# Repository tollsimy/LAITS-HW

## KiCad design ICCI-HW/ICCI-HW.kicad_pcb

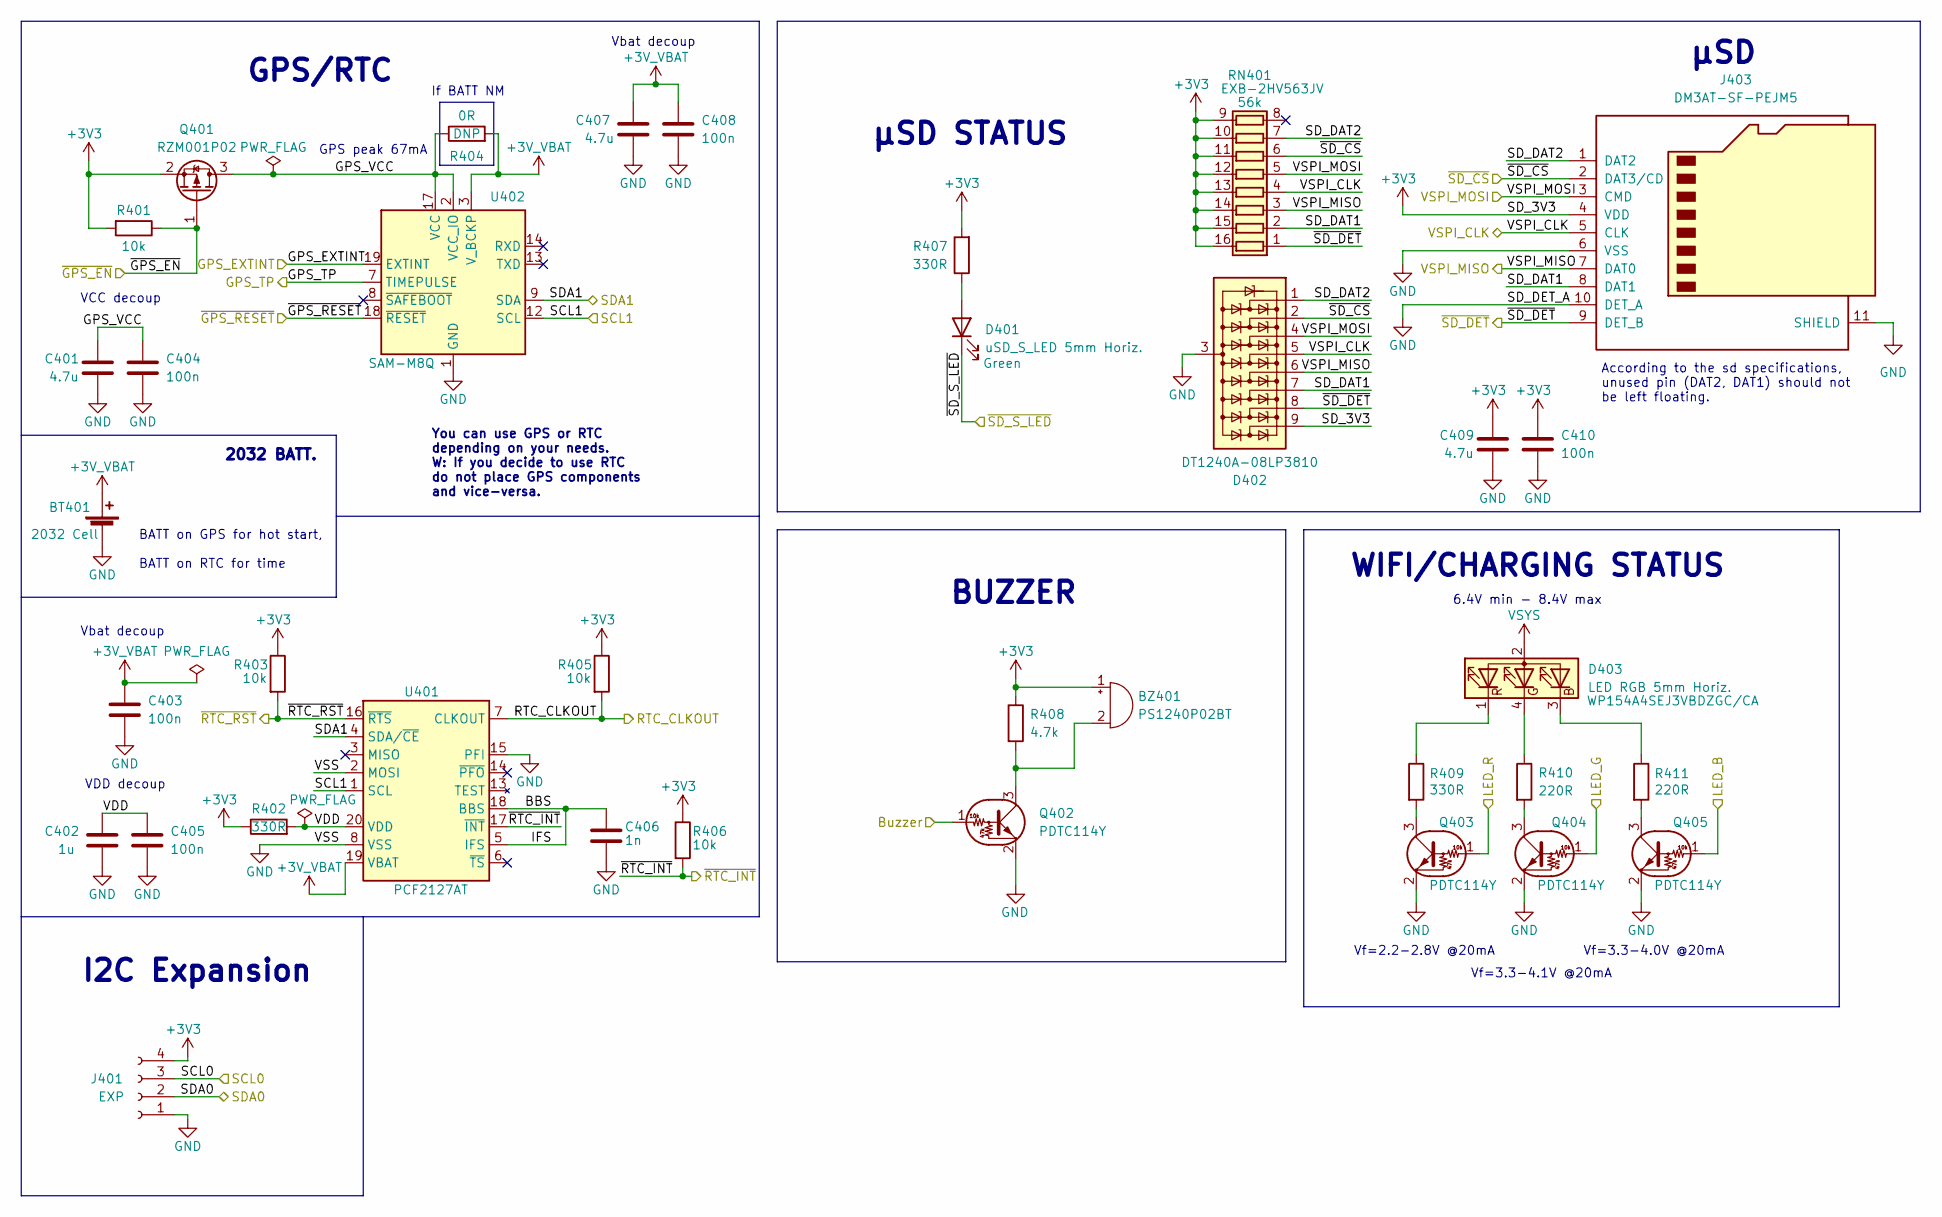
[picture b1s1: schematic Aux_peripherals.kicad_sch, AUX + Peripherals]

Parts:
BT401: 2032 Cell; BatteryHolder_Keystone_3034_1x20mm
BZ401: PS1240P02BT; Buzzer_TDK_PS1240P02BT_D12.2mm_H6.5mm
C401, C407, C409: 4.7u; C_0603_1608Metric
C402: 1u; C_0603_1608Metric
C403, C404, C405, C408, C410: 100n; C_0603_1608Metric
C406: 1n; C_0603_1608Metric
D401: uSD_S_LED 5mm Horiz.; LED_D5.0mm_Horizontal_O3.81mm_Z3.0mm
D402: DT1240A-08LP3810; ICCI_UDFN-9_1.0x3.8mm_P0.5mm
D403: LED RGB 5mm Horiz.; LED_D5.0mm-4_RGB_Staggered_Pins_Horizontal
J401: EXP; PinSocket_2x02_P2.54mm_Horizontal
J403: DM3AT-SF-PEJM5; ICCI_microSD_HC_Hirose_DM3AT-SF-PEJM5
Q401: RZM001P02
Q402, Q403, Q404, Q405: PDTC114Y; SOT-23
R401, R403, R405, R406: 10k; R_0603_1608Metric
R402, R407, R409: 330R; R_0603_1608Metric
R404: 0R; R_0603_1608Metric
R408: 4.7k; R_0603_1608Metric
R410, R411: 220R; R_0603_1608Metric
RN401: 56k; R_Array_Convex_8x0602
U401: PCF2127AT
U402: SAM-M8Q; ICCI_ublox_SAM-M8Q

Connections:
+3V0: BT401.1 (+), C403.1, C407.1, C408.1, R404.2, U401.19 (VBAT), U402.3 (V_BCKP); also elsewhere on the board
+3V3: BZ401.1 (-), C409.1, C410.1, D402.9 (K8), J401.4, J403.4 (VDD), Q401.2 (S), R401.2, R402.1, R403.1, R405.1, R406.1, R407.2, R408.1, RN401.9 (R8.2), RN401.10 (R7.2), RN401.11 (R6.2), RN401.12 (R5.2), RN401.13 (R4.2), RN401.14 (R3.2), RN401.15 (R2.2), RN401.16 (R1.2); also elsewhere on the board
/AUX + Peripherals/BBS: C406.1, U401.5 (IFS), U401.18 (BBS)
/AUX + Peripherals/GPS_EXTINT: U402.19 (EXTINT); also elsewhere on the board
/AUX + Peripherals/GPS_TP: U402.7 (TIMEPULSE); also elsewhere on the board
/AUX + Peripherals/GPS_VCC: C401.1, C404.1, Q401.3 (D), R404.1, U402.2 (VCC_IO), U402.17 (VCC)
/AUX + Peripherals/LED_B: Q405.1 (B); also elsewhere on the board
/AUX + Peripherals/LED_G: Q404.1 (B); also elsewhere on the board
/AUX + Peripherals/LED_R: Q403.1 (B); also elsewhere on the board
/AUX + Peripherals/RTC_CLKOUT: R405.2, U401.7 (CLKOUT); also elsewhere on the board
/AUX + Peripherals/SCL0: J401.3; also elsewhere on the board
/AUX + Peripherals/SCL1: U401.1 (SCL), U402.12 (SCL); also elsewhere on the board
/AUX + Peripherals/SDA0: J401.2; also elsewhere on the board
/AUX + Peripherals/SDA1: U401.4 (SDA/~CE), U402.9 (SDA); also elsewhere on the board
/AUX + Peripherals/SD_DAT1: D402.7 (K6), J403.8 (DAT1), RN401.2 (R2.1)
/AUX + Peripherals/SD_DAT2: D402.1 (K1), J403.1 (DAT2), RN401.7 (R7.1)
/AUX + Peripherals/VDD: C402.1, C405.1, R402.2, U401.20 (VDD)
/AUX + Peripherals/VSPI_CLK: D402.5 (K4), J403.5 (CLK), RN401.4 (R4.1); also elsewhere on the board
/AUX + Peripherals/VSPI_MISO: D402.6 (K5), J403.7 (DAT0), RN401.3 (R3.1); also elsewhere on the board
/AUX + Peripherals/VSPI_MOSI: D402.4 (K3), J403.3 (CMD), RN401.5 (R5.1); also elsewhere on the board
/AUX + Peripherals/~GPS_EN: Q401.1 (G), R401.1; also elsewhere on the board
/AUX + Peripherals/~GPS_RESET: U402.18 (~RESET); also elsewhere on the board
/AUX + Peripherals/~RTC_INT: R406.2, U401.17 (~INT); also elsewhere on the board
/AUX + Peripherals/~RTC_RST: R403.2, U401.16 (~RTS); also elsewhere on the board
/AUX + Peripherals/~SD_CS: D402.2 (K2), J403.2 (DAT3/CD), RN401.6 (R6.1); also elsewhere on the board
/AUX + Peripherals/~SD_DET: D402.8 (K7), J403.9 (DET_B), RN401.1 (R1.1); also elsewhere on the board
/AUX + Peripherals/~SD_S_LED: D401.1 (K); also elsewhere on the board
/ESP/Buzzer: Q402.1 (B); also elsewhere on the board
GND: BT401.2 (-), C401.2, C402.2, C403.2, C404.2, C405.2, C406.2, C407.2, C408.2, C409.2, C410.2, D402.3 (A), J401.1, J403.6 (VSS), J403.10 (DET_A), J403.11 (SHIELD), Q402.2 (E), Q403.2 (E), Q404.2 (E), Q405.2 (E), U401.2 (MOSI), U401.8 (VSS), U401.15 (PFI), U402.1 (GND), U402.4 (GND), U402.5 (GND), U402.6 (GND), U402.10 (GND), U402.11 (GND), U402.15 (GND), U402.16 (GND), U402.20 (GND); also elsewhere on the board
unnamed: BZ401.2 (+), Q402.3 (C), R408.2
unnamed: D401.2 (A), R407.1
unnamed: D403.1 (RK), R409.1
unnamed: D403.3 (BK), R411.1
unnamed: D403.4 (GK), R410.1
unnamed: Q403.3 (C), R409.2
unnamed: Q404.3 (C), R410.2
unnamed: Q405.3 (C), R411.2
VCC: D403.2 (A); also elsewhere on the board

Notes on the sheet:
VCC decoup
Vbat decoup
GPS/RTC
According to the sd specifications, unused pin (DAT2, DAT1) should not be left floating.
You can use GPS or RTC depending on your needs. W: If you decide to use RTC do not place GPS components and vice-versa.
BUZZER
I2C Expansion
6.4V min - 8.4V max
Vf=2.2-2.8V @20mA
If BATT NM
BATT on GPS for hot start, BATT on RTC for time
GPS peak 67mA
μSD STATUS
VDD decoup
Vf=3.3-4.1V @20mA
2032 BATT.
Vf=3.3-4.0V @20mA
WIFI/CHARGING STATUS
μSD

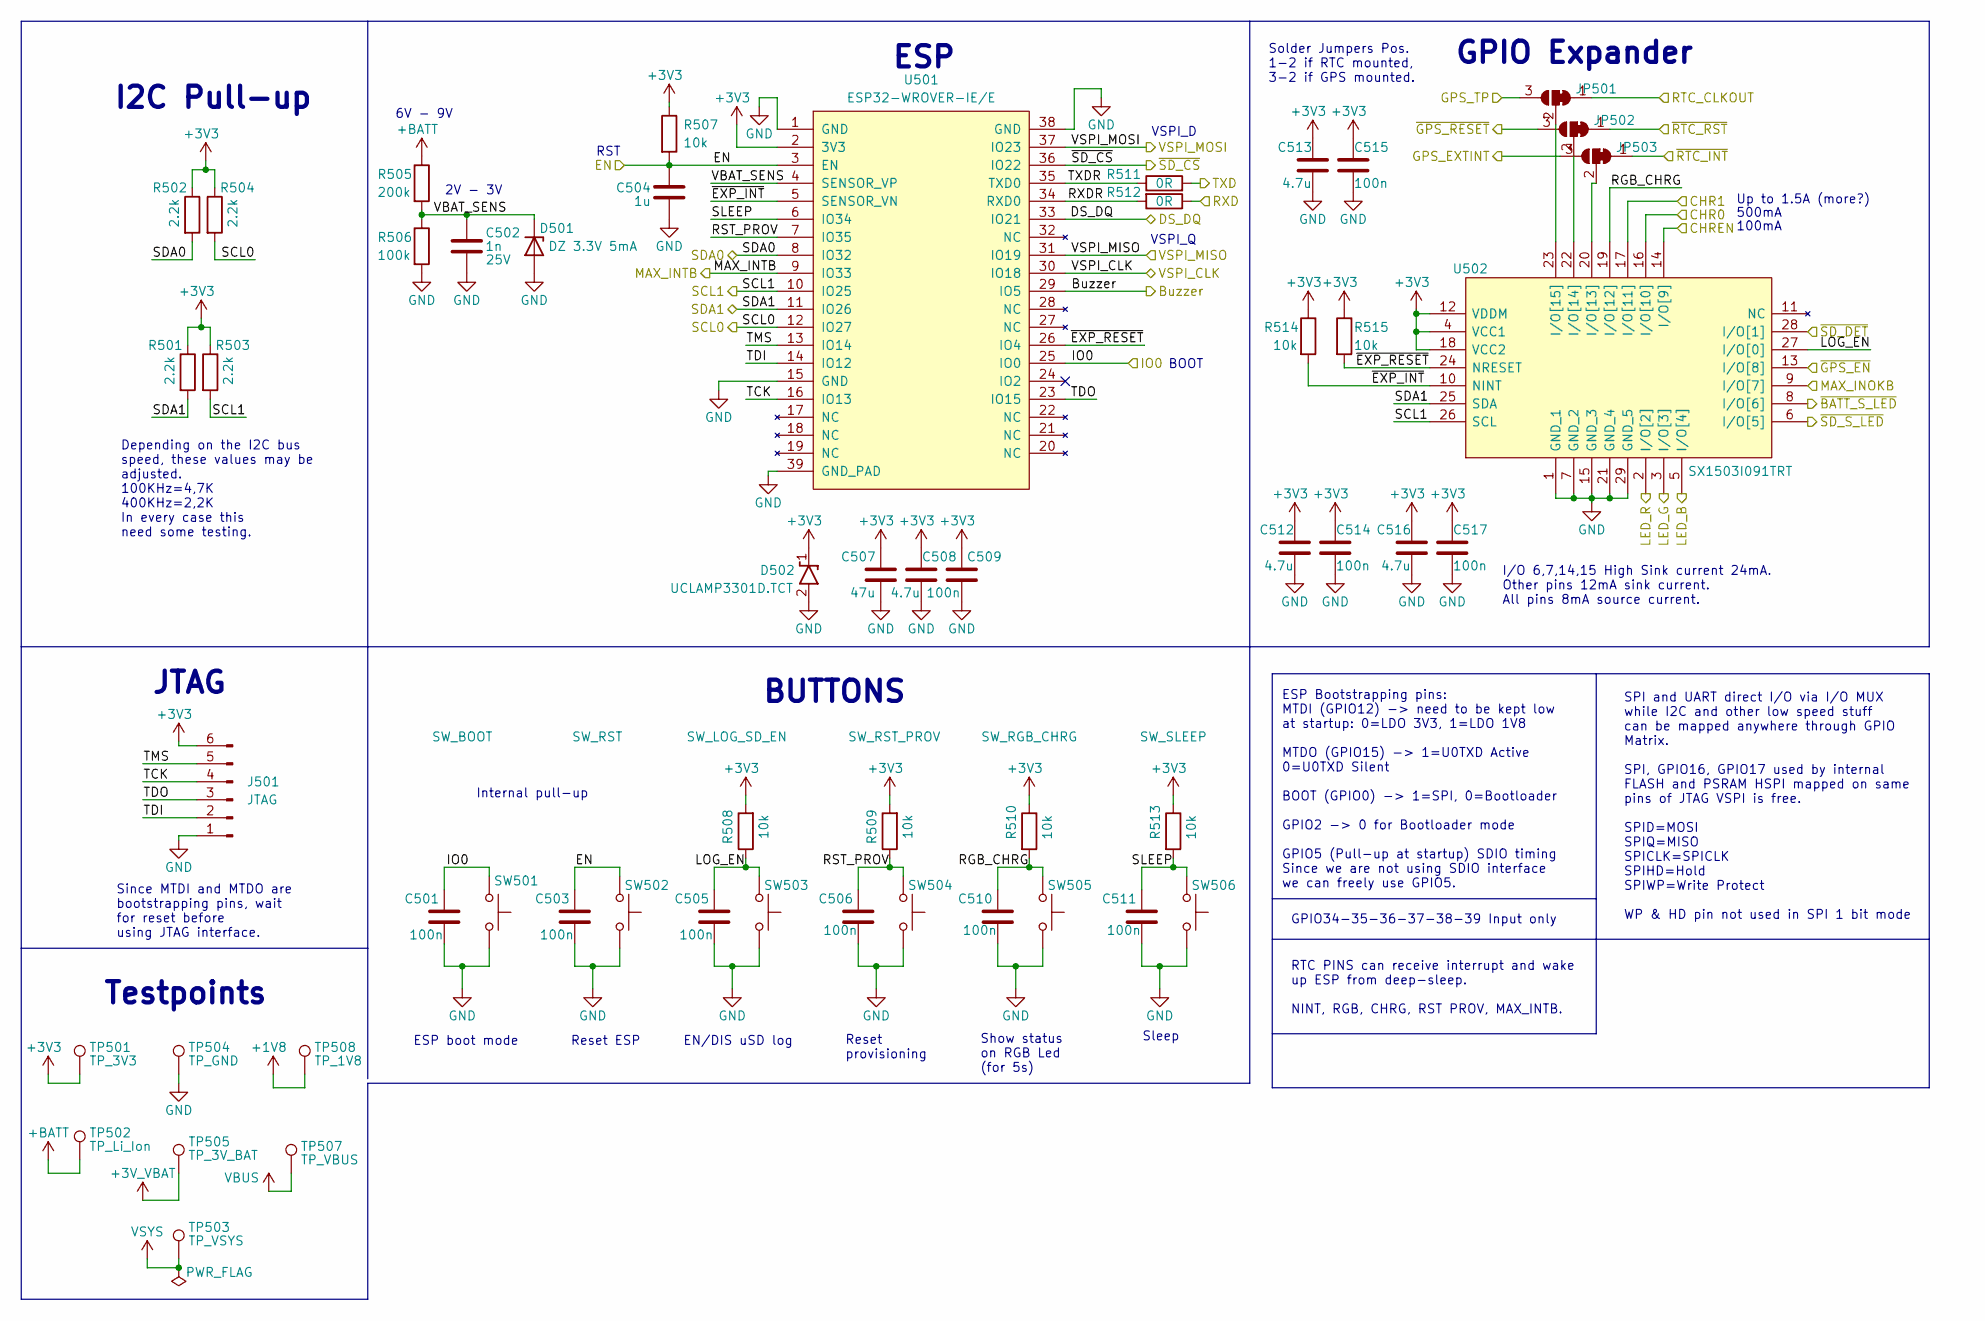
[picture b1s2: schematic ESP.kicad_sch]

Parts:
C501, C503, C505, C506, C509, C510, C511, C514, C515, C517: 100n; C_0603_1608Metric
C502: 1n; C_0603_1608Metric; Voltage Rating 25V
C504: 1u; C_0603_1608Metric
C507: 47u; C_1210_3225Metric
C508, C512, C513, C516: 4.7u; C_0603_1608Metric
D501: DZ 3.3V 5mA; D_SOD-923
D502: UCLAMP3301D.TCT; D_SOD-323
J501: JTAG; JST_B6B-XH-A
JP501, JP502, JP503: SolderJumper_3_Bridged12; SolderJumper-3_P1.3mm_Open_RoundedPad1.0x1.5mm_NumberLabels
R501, R502, R503, R504: 2.2k; R_0603_1608Metric
R505: 200k; R_0603_1608Metric
R506: 100k; R_0603_1608Metric
R507, R508, R509, R510, R513, R514, R515: 10k; R_0603_1608Metric
R511, R512: 0R; R_0603_1608Metric
SW501: SW_BOOT; SW_Tactile_SPST_Angled_PTS645Vx83-2LFS
SW502: SW_RST; SW_Tactile_SPST_Angled_PTS645Vx83-2LFS
SW503: SW_LOG_SD_EN; SW_Tactile_SPST_Angled_PTS645Vx83-2LFS
SW504: SW_RST_PROV; SW_Tactile_SPST_Angled_PTS645Vx83-2LFS
SW505: SW_RGB_CHRG; SW_Tactile_SPST_Angled_PTS645Vx83-2LFS
SW506: SW_SLEEP; SW_Tactile_SPST_Angled_PTS645Vx83-2LFS
TP501: TP_3V3; TestPoint_THTPad_D1.5mm_Drill0.7mm
TP502: TP_Li_Ion; TestPoint_THTPad_D1.5mm_Drill0.7mm
TP503: TP_VSYS; TestPoint_THTPad_D1.5mm_Drill0.7mm
TP504: TP_GND; TestPoint_THTPad_D1.5mm_Drill0.7mm
TP505: TP_3V_BAT; TestPoint_THTPad_D1.5mm_Drill0.7mm
TP507: TP_VBUS; TestPoint_THTPad_D1.5mm_Drill0.7mm
TP508: TP_1V8; TestPoint_THTPad_D1.5mm_Drill0.7mm
U501: ESP32-WROVER-IE/E; ESP32-WROVER-IE
U502: SX1503I091TRT

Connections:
+1V8: TP508.1; also elsewhere on the board
+3V0: TP505.1; also elsewhere on the board
+3V3: C507.1, C508.1, C509.1, C512.1, C513.1, C514.1, C515.1, C516.1, C517.1, D502.1, J501.6, R501.1, R502.1, R503.1, R504.1, R507.1, R508.2, R509.2, R510.1, R513.1, R514.1, R515.1, TP501.1, U501.2 (3V3), U502.4 (VCC1), U502.12 (VDDM), U502.18 (VCC2); also elsewhere on the board
+BATT: R505.1, TP502.1; also elsewhere on the board
/AUX + Peripherals/GPS_EXTINT: JP503.3 (B); also elsewhere on the board
/AUX + Peripherals/GPS_TP: JP501.3 (B); also elsewhere on the board
/AUX + Peripherals/LED_B: U502.5 (I/O[4]); also elsewhere on the board
/AUX + Peripherals/LED_G: U502.3 (I/O[3]); also elsewhere on the board
/AUX + Peripherals/LED_R: U502.2 (I/O[2]); also elsewhere on the board
/AUX + Peripherals/RTC_CLKOUT: JP501.1 (A); also elsewhere on the board
/AUX + Peripherals/SCL0: R502.2, U501.8 (IO32); also elsewhere on the board
/AUX + Peripherals/SCL1: R503.2, U501.10 (IO25), U502.26 (SCL); also elsewhere on the board
/AUX + Peripherals/SDA0: R504.2, U501.12 (IO27); also elsewhere on the board
/AUX + Peripherals/SDA1: R501.2, U501.11 (IO26), U502.25 (SDA); also elsewhere on the board
/AUX + Peripherals/VSPI_CLK: U501.30 (IO18); also elsewhere on the board
/AUX + Peripherals/VSPI_MISO: U501.31 (IO19); also elsewhere on the board
/AUX + Peripherals/VSPI_MOSI: U501.37 (IO23); also elsewhere on the board
/AUX + Peripherals/~GPS_EN: U502.13 (I/O[8]); also elsewhere on the board
/AUX + Peripherals/~GPS_RESET: JP502.3 (B); also elsewhere on the board
/AUX + Peripherals/~RTC_INT: JP503.1 (A); also elsewhere on the board
/AUX + Peripherals/~RTC_RST: JP502.1 (A); also elsewhere on the board
/AUX + Peripherals/~SD_CS: U501.36 (IO22); also elsewhere on the board
/AUX + Peripherals/~SD_DET: U502.28 (I/O[1]); also elsewhere on the board
/AUX + Peripherals/~SD_S_LED: U502.6 (I/O[5]); also elsewhere on the board
/BATT + POWER/MAX_INOKB: U502.9 (I/O[7]); also elsewhere on the board
/BATT + POWER/MAX_INTB: U501.9 (IO33); also elsewhere on the board
/BATT + POWER/~BATT_S_LED: U502.8 (I/O[6]); also elsewhere on the board
/ESP/Buzzer: U501.29 (IO5); also elsewhere on the board
/ESP/DS_DQ: U501.33 (IO21); also elsewhere on the board
/ESP/EN: C503.2, C504.1, R507.2, SW502.1, U501.3 (EN); also elsewhere on the board
/ESP/IO0: C501.2, SW501.1, U501.25 (IO0); also elsewhere on the board
/ESP/LOG_EN: C505.2, R508.1, SW503.1, U502.27 (I/O[0])
/ESP/RGB_CHRG: C510.2, R510.2, SW505.1, U502.19 (I/O[12])
/ESP/RST_PROV: C506.2, R509.1, SW504.1, U501.7 (IO35)
/ESP/RXDR: R512.2, U501.34 (RXD0)
/ESP/SLEEP: C511.2, R513.2, SW506.1, U501.6 (IO34)
/ESP/TCK: J501.4, U501.16 (IO13)
/ESP/TDI: J501.2, U501.14 (IO12)
/ESP/TDO: J501.3, U501.23 (IO15)
/ESP/TMS: J501.5, U501.13 (IO14)
/ESP/TXDR: R511.1, U501.35 (TXD0)
/ESP/VBAT_SENS: C502.1, D501.1 (K), R505.2, R506.1, U501.4 (SENSOR_VP)
/ESP/~EXP_INT: R514.2, U501.5 (SENSOR_VN), U502.10 (NINT)
/ESP/~EXP_RESET: R515.2, U501.26 (IO4), U502.24 (NRESET)
/USB/CHR0: U502.16 (I/O[10]); also elsewhere on the board
/USB/CHR1: U502.17 (I/O[11]); also elsewhere on the board
/USB/CHREN: U502.14 (I/O[9]); also elsewhere on the board
/USB/RXD: R512.1; also elsewhere on the board
/USB/TXD: R511.2; also elsewhere on the board
GND: C501.1, C502.2, C503.1, C504.2, C505.1, C506.1, C507.2, C508.2, C509.2, C510.1, C511.1, C512.2, C513.2, C514.2, C515.2, C516.2, C517.2, D501.2 (A), D502.2, J501.1, R506.2, SW501.2, SW502.2, SW503.2, SW504.2, SW505.2, SW506.2, TP504.1, U501.1 (GND), U501.15 (GND), U501.38 (GND), U501.39 (GND_PAD), U502.1 (GND_1), U502.7 (GND_2), U502.15 (GND_3), U502.21 (GND_4), U502.29 (GND_5); also elsewhere on the board
unnamed: JP501.2 (C), U502.23 (I/O[15])
unnamed: JP502.2 (C), U502.22 (I/O[14])
unnamed: JP503.2 (C), U502.20 (I/O[13])
VBUS: TP507.1; also elsewhere on the board
VCC: TP503.1; also elsewhere on the board

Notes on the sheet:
Reset provisioning
BUTTONS
RST
Depending on the I2C bus speed, these values may be adjusted. 100KHz=4,7K 400KHz=2,2K In every case this need some testing.
JTAG
Up to 1.5A (more?)
I2C Pull-up
BOOT
ESP boot mode
100mA
ESP Bootstrapping pins: MTDI (GPIO12) -> need to be kept low at startup: 0=LDO 3V3, 1=LDO 1V8 MTDO (GPIO15) -> 1=U0TXD Active 0=U0TXD Silent BOOT (GPIO0) -> 1=SPI, 0=Bootloader GPIO2 -> 0 for Bootloader mode GPIO5 (Pull-up at startup) SDIO timing Since we are not using SDIO interface we can freely 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
EN/DIS uSD log
Testpoints
6V - 9V
RTC PINS can receive interrupt and wake up ESP from deep-sleep. NINT, RGB, CHRG, RST PROV, MAX_INTB.
GPIO Expander
Reset ESP
VSPI_D
I/O 6,7,14,15 High Sink current 24mA. Other pins 12mA sink current. All pins 8mA source current.
Since MTDI and MTDO are bootstrapping pins, wait for reset before using JTAG interface.
500mA
Show status on RGB Led (for 5s)
Sleep
ESP
2V - 3V
Internal pull-up
Solder Jumpers Pos. 1-2 if RTC mounted, 3-2 if GPS mounted.
SPI and UART direct I/O via I/O MUX while I2C and other low speed stuff can be mapped anywhere through GPIO Matrix. SPI, GPIO16, GPIO17 used by internal FLASH and PSRAM HSPI mapped on same pins of JTAG VSPI is free. SPID=MOSI SPIQ=MISO SPICLK=SPICLK SPIHD=Hold SPIWP=Write Protect WP & HD pin not us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
VSPI_Q
GPIO34-35-36-37-38-39 Input only

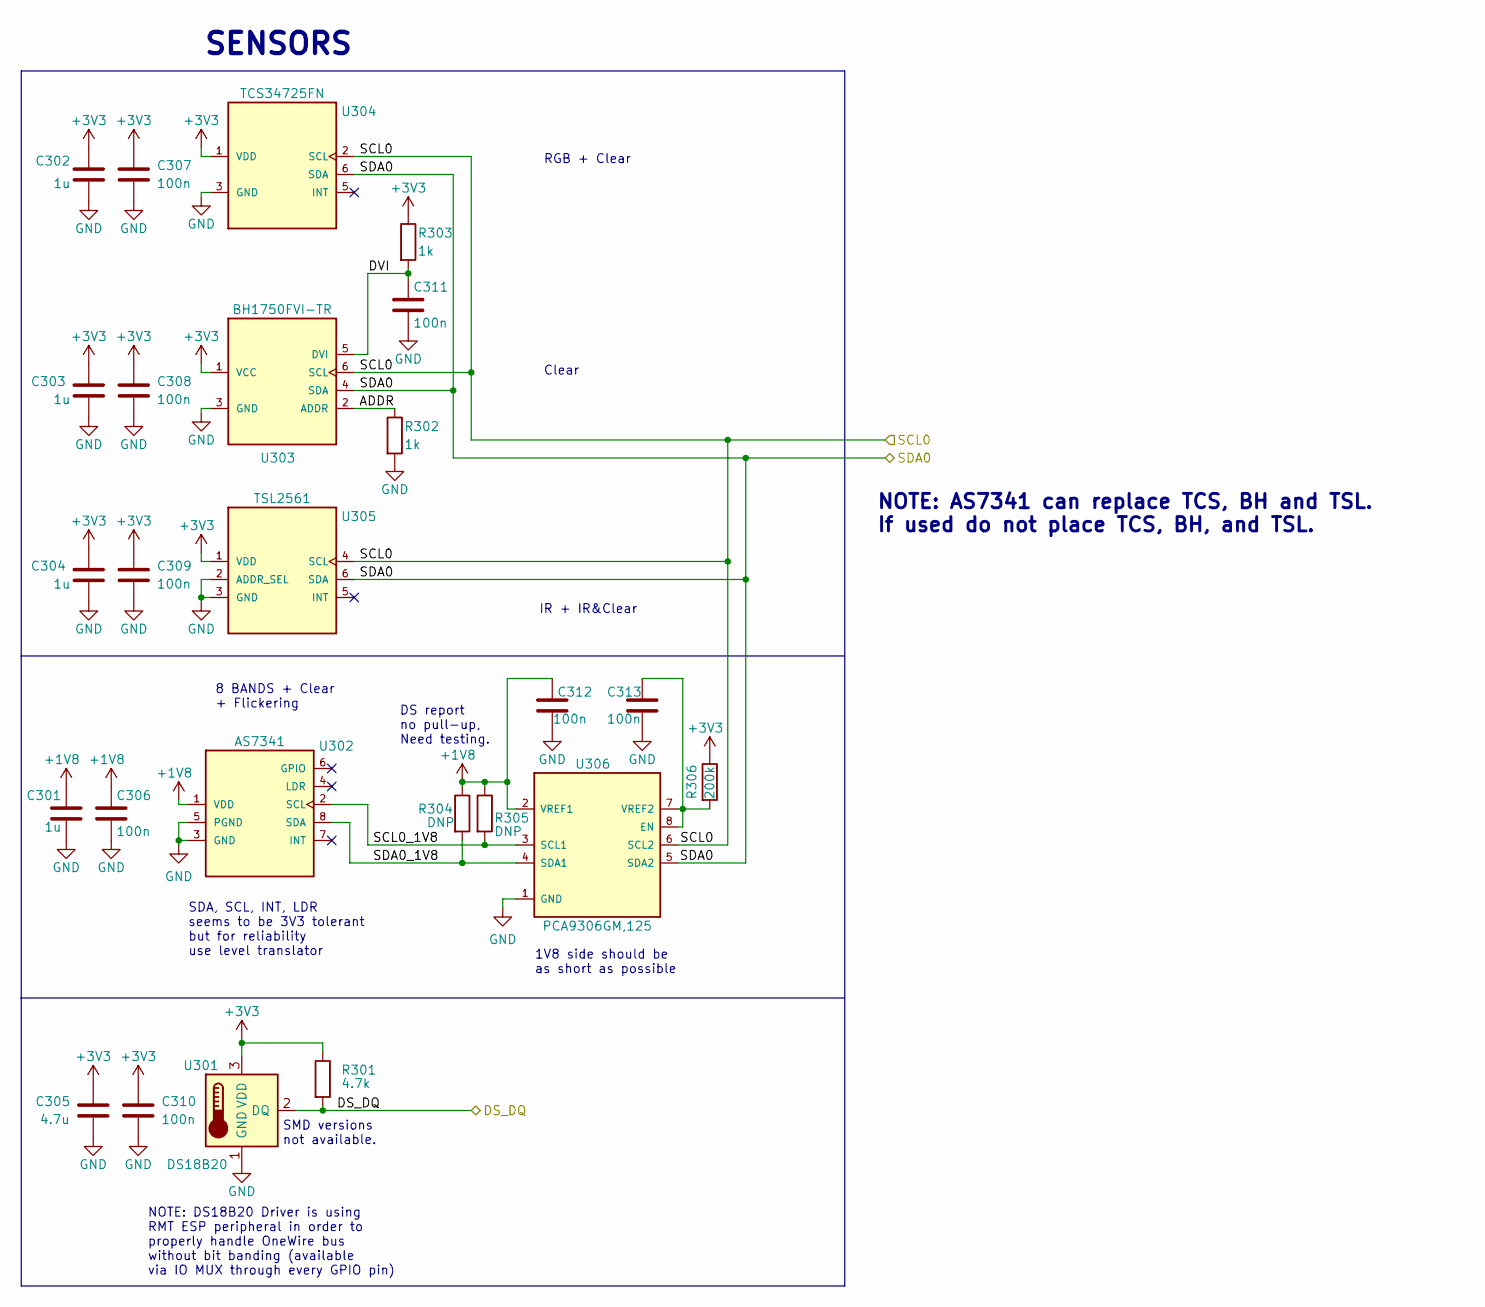
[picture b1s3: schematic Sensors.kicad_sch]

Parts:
C301, C302, C303, C304: 1u; C_0603_1608Metric
C305: 4.7u; C_0603_1608Metric
C306, C307, C308, C309, C310, C311, C312, C313: 100n; C_0603_1608Metric
R301: 4.7k; R_0603_1608Metric
R302, R303: 1k; R_0603_1608Metric
R304, R305: DNP; R_0603_1608Metric
R306: 200k; R_0603_1608Metric
U301: DS18B20; DS18B20 Hor.
U302: AS7341; AS7431
U303: BH1750FVI-TR
U304: TCS34725FN
U305: TSL2561
U306: PCA9306GM,125; PCA9306GM; Manufacturer_Part_Number PCA9306GM,125; Mouser Part Number 771-PCA9306GM125

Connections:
+1V8: C301.1, C306.1, C312.1, R304.1, R305.1, U302.1 (VDD), U306.2 (VREF1); also elsewhere on the board
+3V3: C302.1, C303.1, C304.1, C305.1, C307.1, C308.1, C309.1, C310.1, R301.1, R303.1, R306.1, U301.3 (VDD), U303.1 (VCC), U304.1 (VDD), U305.1 (VDD); also elsewhere on the board
/AUX + Peripherals/SCL0: U303.6 (SCL), U304.2 (SCL), U305.4 (SCL), U306.6 (SCL2); also elsewhere on the board
/AUX + Peripherals/SDA0: U303.4 (SDA), U304.6 (SDA), U305.6 (SDA), U306.5 (SDA2); also elsewhere on the board
/ESP/DS_DQ: R301.2, U301.2 (DQ); also elsewhere on the board
/Sensors/ADDR: R302.1, U303.2 (ADDR)
/Sensors/DVI: C311.1, R303.2, U303.5 (DVI)
/Sensors/SCL0_1V8: R305.2, U302.2 (SCL), U306.3 (SCL1)
/Sensors/SDA0_1V8: R304.2, U302.8 (SDA), U306.4 (SDA1)
GND: C301.2, C302.2, C303.2, C304.2, C305.2, C306.2, C307.2, C308.2, C309.2, C310.2, C311.2, C312.2, C313.2, R302.2, U301.1 (GND), U302.3 (GND), U302.5 (PGND), U303.3 (GND), U304.3 (GND), U305.2 (ADDR_SEL), U305.3 (GND), U306.1 (GND); also elsewhere on the board
unnamed: C313.1, R306.2, U306.7 (VREF2), U306.8 (EN)

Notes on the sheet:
RGB + Clear
Clear
1V8 side should be as short as possible
NOTE: AS7341 can replace TCS, BH and TSL. If used do not place TCS, BH, and TSL.
IR + IR&Clear
SDA, SCL, INT, LDR seems to be 3V3 tolerant but for reliability use level translator
8 BANDS + Clear + Flickering
DS report no pull-up, Need testing.
SMD versions not available.
SENSORS
NOTE: DS18B20 Driver is using RMT ESP peripheral in order to properly handle OneWire bus without bit banding (available via IO MUX through every GPIO pin)

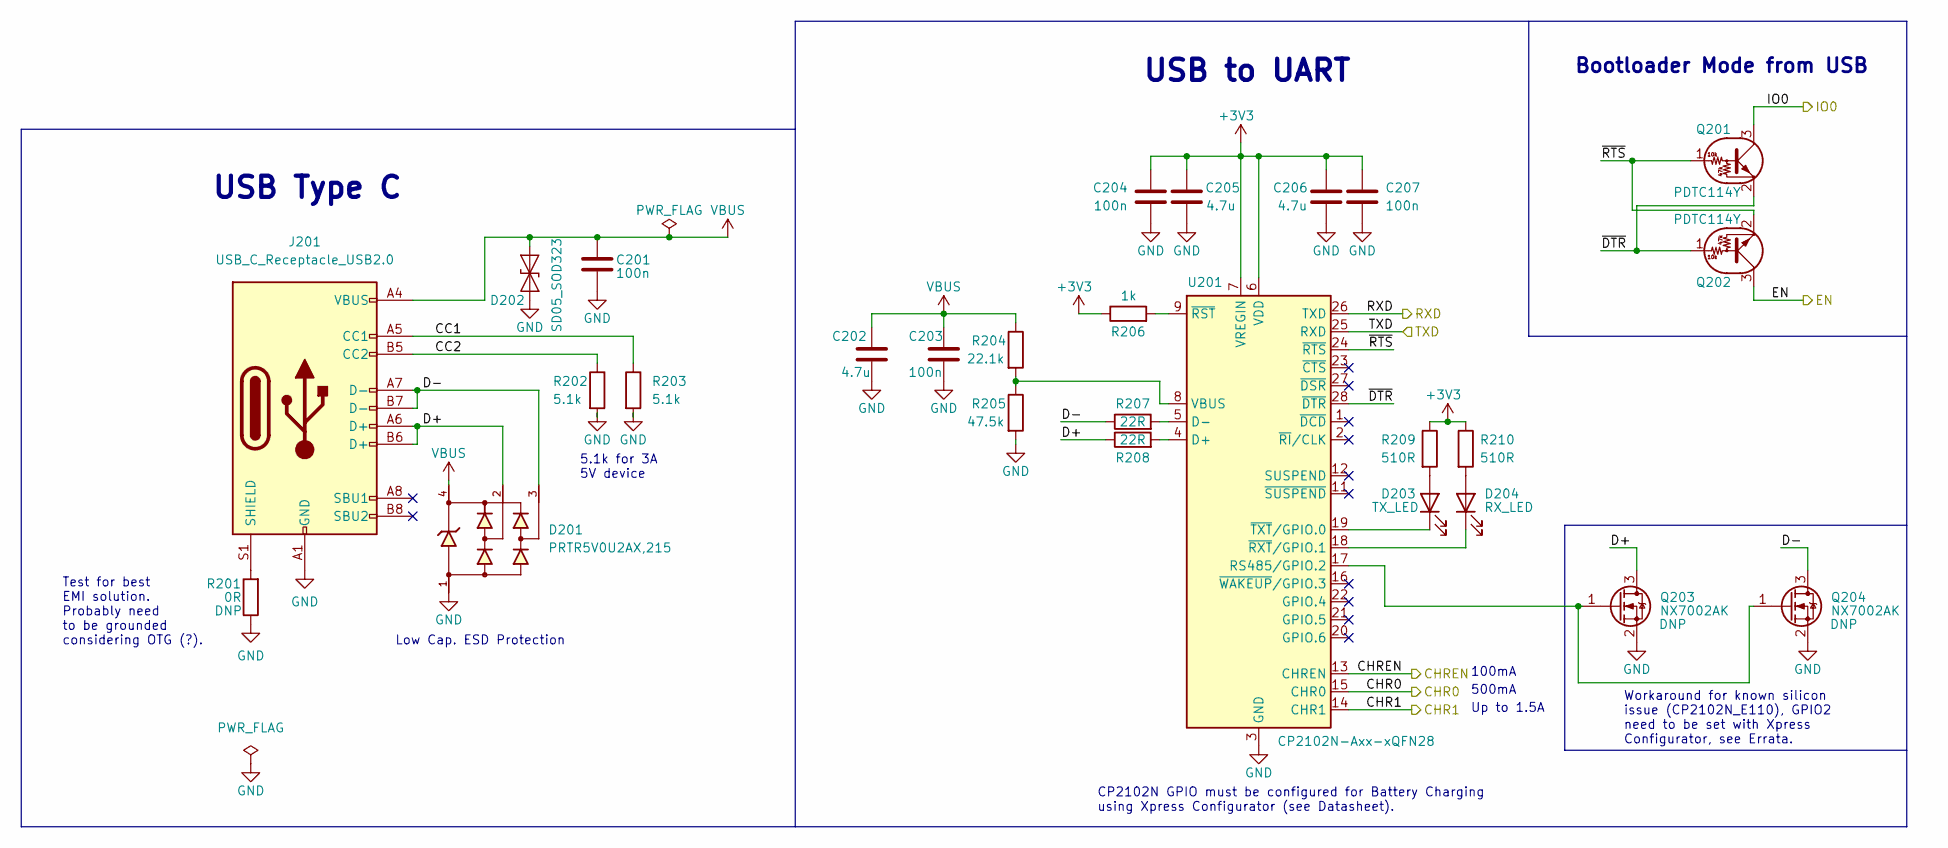
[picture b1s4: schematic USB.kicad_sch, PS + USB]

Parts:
C201, C203, C204, C207: 100n; C_0603_1608Metric
C202, C205, C206: 4.7u; C_0603_1608Metric
D201: PRTR5V0U2AX,215; SOT-143
D202: SD05_SOD323; D_SOD-323
D203: TX_LED; LED_0805_2012Metric
D204: RX_LED; LED_0805_2012Metric
J201: USB_C_Receptacle_USB2.0; USB_C_Receptacle_Amphenol_12401548E4-2A
Q201, Q202: PDTC114Y; SOT-23
Q203, Q204: NX7002AK; SOT-23
R201: 0R; R_0603_1608Metric
R202, R203: 5.1k; R_0603_1608Metric
R204: 22.1k; R_0603_1608Metric
R205: 47.5k; R_0603_1608Metric
R206: 1k; R_0603_1608Metric
R207, R208: 22R; R_0603_1608Metric
R209, R210: 510R; R_0603_1608Metric
U201: CP2102N-Axx-xQFN28; QFN-28-1EP_5x5mm_P0.5mm_EP3.35x3.35mm

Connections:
+3V3: C204.1, C205.1, C206.1, C207.1, R206.1, R209.1, R210.1, U201.6 (VDD), U201.7 (VREGIN); also elsewhere on the board
/ESP/EN: Q202.3 (C); also elsewhere on the board
/ESP/IO0: Q201.3 (C); also elsewhere on the board
/USB/CC1: J201.A5 (CC1), R203.1
/USB/CC2: J201.B5 (CC2), R202.1
/USB/CHR0: U201.15 (CHR0); also elsewhere on the board
/USB/CHR1: U201.14 (CHR1); also elsewhere on the board
/USB/CHREN: U201.13 (CHREN); also elsewhere on the board
/USB/D+: D201.2, J201.A6 (D+), J201.B6 (D+), Q203.3 (D), R208.1
/USB/D-: D201.3, J201.A7 (D-), J201.B7 (D-), Q204.3 (D), R207.1
/USB/RXD: U201.26 (TXD); also elsewhere on the board
/USB/TXD: U201.25 (RXD); also elsewhere on the board
/USB/~DTR: Q201.2 (E), Q202.1 (B), U201.28 (~DTR)
/USB/~RTS: Q201.1 (B), Q202.2 (E), U201.24 (~RTS)
GND: C201.2, C202.2, C203.2, C204.2, C205.2, C206.2, C207.2, D201.1, D202.1 (A1), J201.A1 (GND), J201.A12 (GND), J201.B1 (GND), J201.B12 (GND), Q203.2 (S), Q204.2 (S), R201.1, R202.2, R203.2, R205.2, U201.3 (GND), U201.29 (GND); also elsewhere on the board
unnamed: D203.1 (K), U201.19 (~TXT/GPIO.0)
unnamed: D203.2 (A), R209.2
unnamed: D204.1 (K), U201.18 (~RXT/GPIO.1)
unnamed: D204.2 (A), R210.2
unnamed: J201.S1 (SHIELD), R201.2
unnamed: Q203.1 (G), Q204.1 (G), U201.17 (RS485/GPIO.2)
unnamed: R204.2, R205.1, U201.8 (VBUS)
unnamed: R206.2, U201.9 (~RST)
unnamed: R207.2, U201.5 (D-)
unnamed: R208.2, U201.4 (D+)
VBUS: C201.1, C202.1, C203.1, D201.4, D202.2 (A2), J201.A4 (VBUS), J201.A9 (VBUS), J201.B4 (VBUS), J201.B9 (VBUS), R204.1; also elsewhere on the board

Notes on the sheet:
Test for best EMI solution. Probably need to be grounded considering OTG (?).
Workaround for known silicon issue (CP2102N_E110), GPIO2 need to be set with Xpress Configurator, see Errata.
USB Type C
CP2102N GPIO must be configured for Battery Charging using Xpress Configurator (see Datasheet).
Bootloader Mode from USB
Low Cap. ESD Protection
USB to UART
500mA
Up to 1.5A
100mA
5.1k for 3A 5V device
